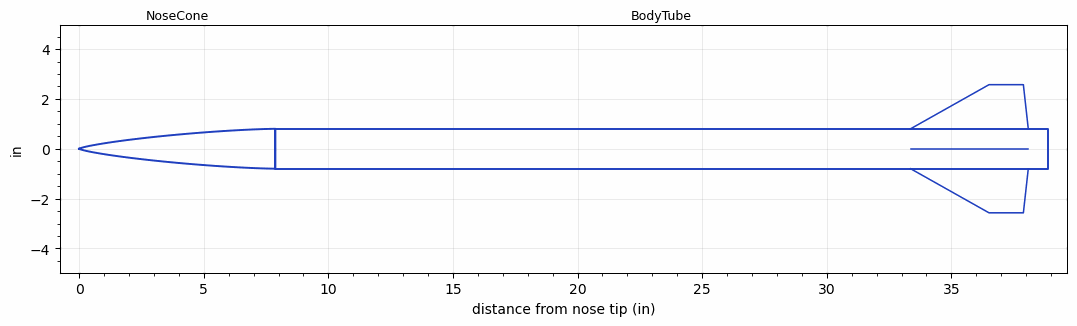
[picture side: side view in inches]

<RASAeroDocument>
 <FileVersion>2</FileVersion>
 <RocketDesign>
  <NoseCone>
   <Length>7.874</Length>
   <Diameter>1.6</Diameter>
   <Shape>Von Karman Ogive</Shape>
   <Location>0</Location>
  </NoseCone>
  <BodyTube>
   <Length>31</Length>
   <Diameter>1.6</Diameter>
   <Location>7.874</Location>
   <Fin>
    <Count>4</Count>
    <Chord>4.7244</Chord>
    <Span>1.7717</Span>
    <SweepDistance>3.1496</SweepDistance>
    <TipChord>1.378</TipChord>
    <Thickness>0.0787</Thickness>
    <LERadius>0.01</LERadius>
    <Location>5.5118</Location>
    <AirfoilSection>Hexagonal</AirfoilSection>
    <FX1>0.5</FX1>
    <FX3>0.5</FX3>
   </Fin>
  </BodyTube>
  <Surface>Rough Camouflage Paint</Surface>
  <ModifiedBarrowman>True</ModifiedBarrowman>
  <Turbulence>True</Turbulence>
  <UseBooster1>False</UseBooster1>
  <UseBooster2>False</UseBooster2>
 </RocketDesign>
 <LaunchSite>
  <Altitude>0</Altitude>
  <Pressure>0</Pressure>
  <RodAngle>0</RodAngle>
  <RodLength>4</RodLength>
  <Temperature>74</Temperature>
  <WindSpeed>0</WindSpeed>
 </LaunchSite>
 <Recovery>
  <Altitude1>1000</Altitude1>
  <Altitude2>1000</Altitude2>
  <DeviceType1>None</DeviceType1>
  <DeviceType2>None</DeviceType2>
  <Event1>False</Event1>
  <Event2>False</Event2>
  <Size1>1</Size1>
  <Size2>1</Size2>
  <EventType1>None</EventType1>
  <EventType2>None</EventType2>
  <CD1>1.33</CD1>
  <CD2>1.33</CD2>
 </Recovery>
 <SimulationList>
  <Simulation>
   <SustainerEngine>H550  (AT)</SustainerEngine>
   <SustainerLaunchWt>2.09</SustainerLaunchWt>
   <SustainerCG>24.3</SustainerCG>
   <SustainerIgnitionDelay>0</SustainerIgnitionDelay>
   <Booster1SeparationDelay>0</Booster1SeparationDelay>
   <Booster1IgnitionDelay>0</Booster1IgnitionDelay>
   <IncludeBooster1>False</IncludeBooster1>
   <Booster2Delay>0</Booster2Delay>
   <IncludeBooster2>False</IncludeBooster2>
   <TimetoApogee>16.12027</TimetoApogee>
   <MaxAltitude>5832.035</MaxAltitude>
   <MaxVelocity>1120.086</MaxVelocity>
  </Simulation>
 </SimulationList>
</RASAeroDocument>
